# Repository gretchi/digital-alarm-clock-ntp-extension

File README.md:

# digital-alarm-clock-ntp-extension

## ボタン配置

## フロー

### ブート

1. ネットワーク確立
2. NTP日時取得

### 電源投入直後

1. `Btn_1` High -> Low (時計を開始)

### 日時合わせ

1. ボタン操作回数を計算し、操作開始をスケジュール
    1. ssが正時となるタイミングにmm + 1回目のエミュレートが行われるようエミュレート開始タイミングをスケジュール
2. `Btn_1` High -> Low
3. `Btn_A` hh++
4. `Btn_B` mm++

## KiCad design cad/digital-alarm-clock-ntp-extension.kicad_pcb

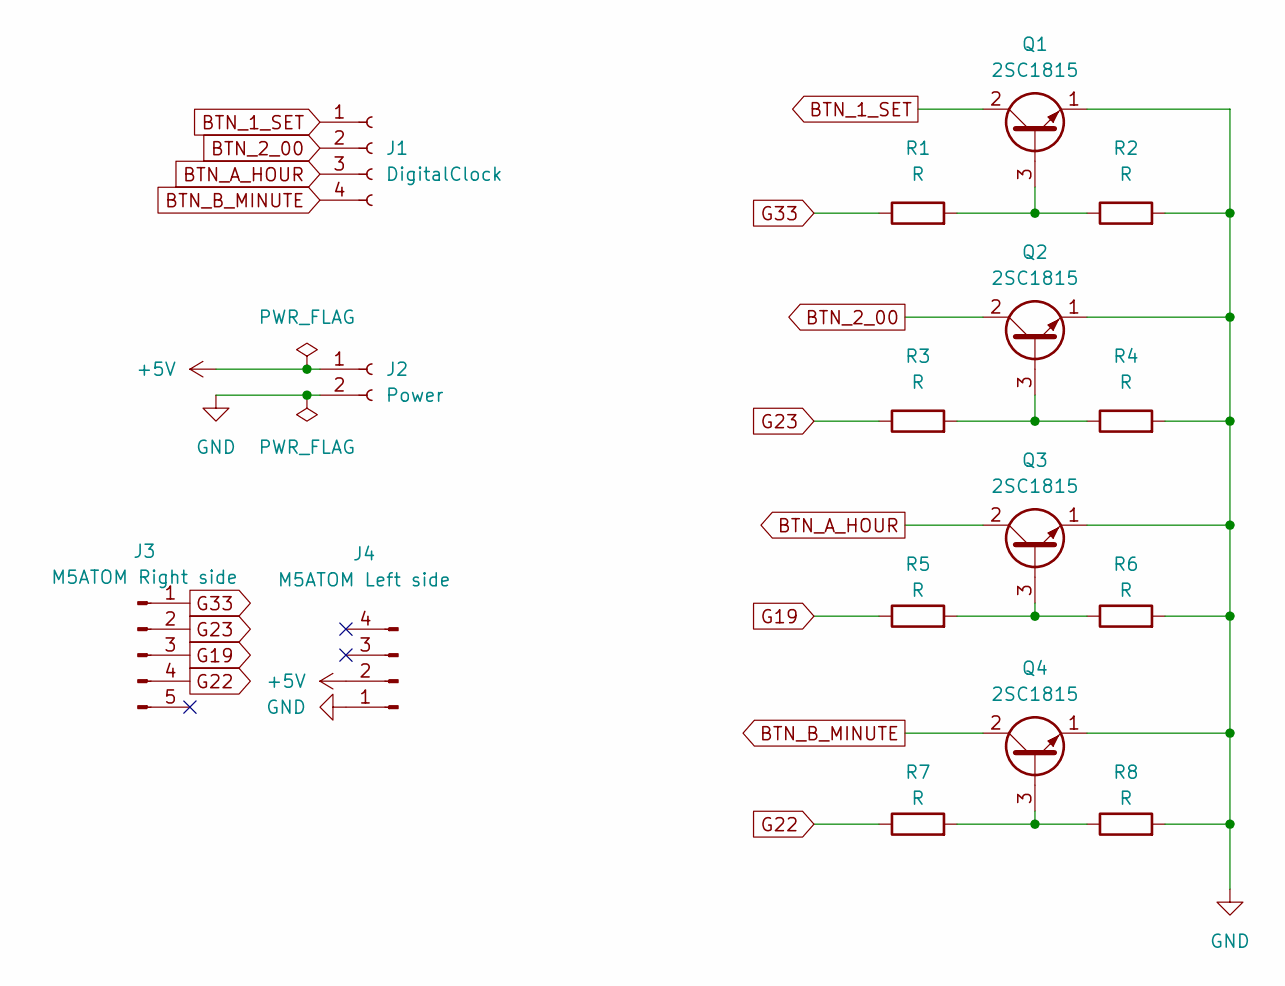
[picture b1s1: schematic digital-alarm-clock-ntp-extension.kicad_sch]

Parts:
J1: DigitalClock; JST_XH_B4B-XH-A_1x04_P2.50mm_Vertical
J2: Power; JST_XH_B2B-XH-A_1x02_P2.50mm_Vertical
J3: M5ATOM Right side; PinHeader_1x05_P2.54mm_Vertical
J4: M5ATOM Left side; PinHeader_1x04_P2.54mm_Vertical
Q1, Q2, Q3, Q4: 2SC1815; TO-92_Inline_Wide
R1, R3, R5, R7: R; R_Axial_DIN0207_L6.3mm_D2.5mm_P10.16mm_Horizontal
R2, R4, R6, R8: R; R_Axial_DIN0204_L3.6mm_D1.6mm_P5.08mm_Vertical

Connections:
+5V: J2.1, J4.2
BTN_1_SET: J1.1, Q1.2 (C)
BTN_2_00: J1.2, Q2.2 (C)
BTN_A_HOUR: J1.3, Q3.2 (C)
BTN_B_MINUTE: J1.4, Q4.2 (C)
G19: J3.3, R5.1
G22: J3.4, R7.1
G23: J3.2, R3.1
G33: J3.1, R1.1
GND: J2.2, J4.1, Q1.1 (E), Q2.1 (E), Q3.1 (E), Q4.1 (E), R2.2, R4.2, R6.2, R8.2
unnamed: Q1.3 (B), R1.2, R2.1
unnamed: Q2.3 (B), R3.2, R4.1
unnamed: Q3.3 (B), R5.2, R6.1
unnamed: Q4.3 (B), R7.2, R8.1

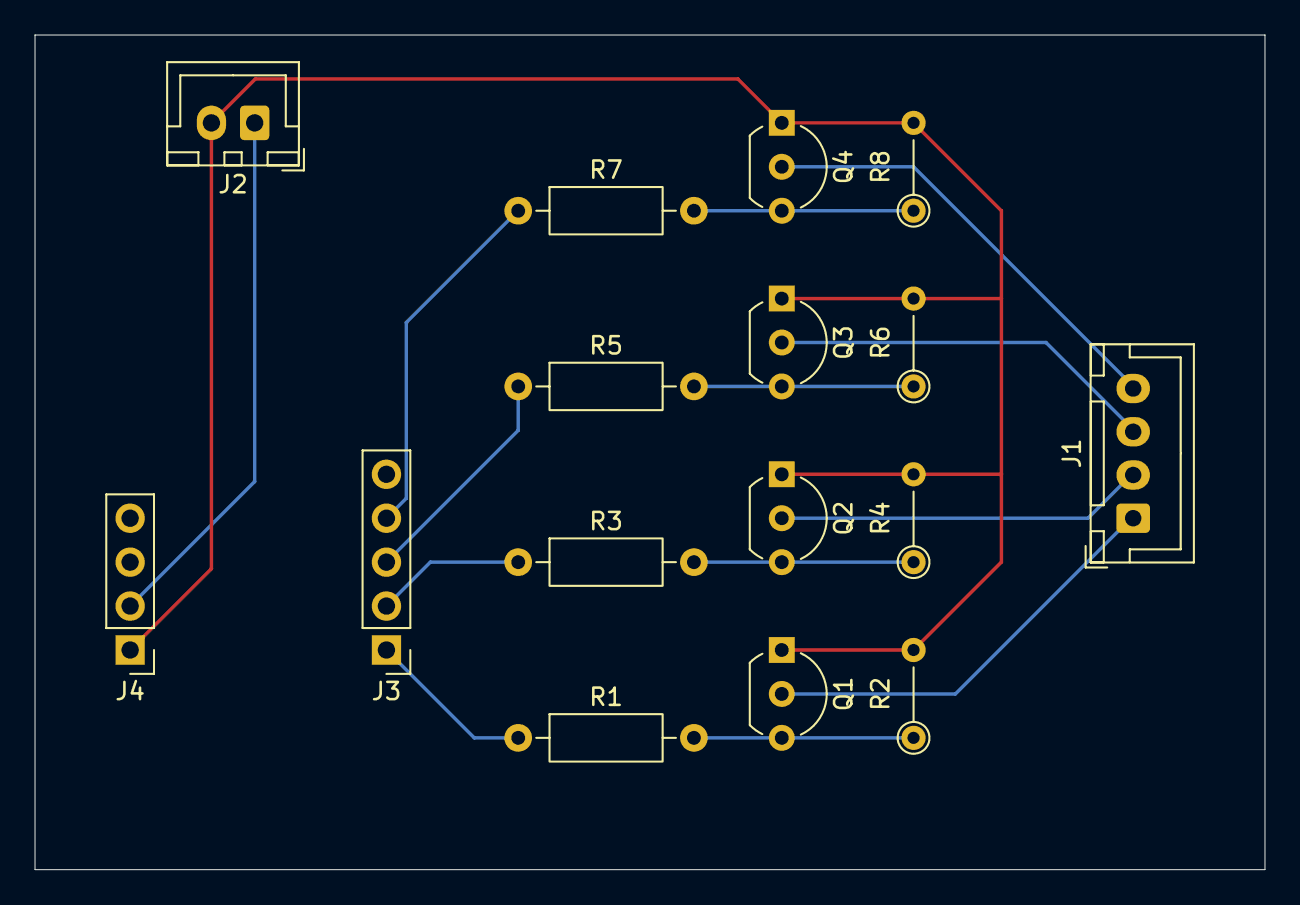
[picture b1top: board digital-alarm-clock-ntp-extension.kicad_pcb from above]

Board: 2 copper layers, 71.1 x 48.3 mm, 16 parts (0 on the bottom side), 14 nets.

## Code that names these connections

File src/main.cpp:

#include <Arduino.h>
#include <M5Atom.h>
#include <WiFiManager.h>
#include <WiFi.h>
#include "app_wifi.h"

const int BTN_1_SET = 33;
const int BTN_2_00 = 23;
const int BTN_A_HOUR = 19;
const int BTN_B_MINUTE = 22;
const int PRESS_MS = 100;

extern WiFiManager wm;
extern String configure_ssid;
extern String configure_password;

void press_ms(int gpio, int ms);

void setup()
{
    M5.begin(true, false, true);
    Serial.begin(115200);
    M5.dis.drawpix(0, 0xFF0000);

    pinMode(BTN_1_SET, INPUT);
    pinMode(BTN_2_00, INPUT);
    pinMode(BTN_A_HOUR, INPUT);
    pinMode(BTN_B_MINUTE, INPUT);

    initAppWiFi();
    Serial.printf("Configure Wi-Fi SSID: %s, Password: %s\n", configure_ssid.c_str(), configure_password.c_str());
    if (WiFiConnect() == 0)
    {
        Serial.println("Wi-Fi not connecting");
    }
    M5.dis.drawpix(0, 0x008000);

    press_ms(BTN_1_SET, PRESS_MS);
    delay(5000);

    press_ms(BTN_1_SET, PRESS_MS);
    for (int i = 0; i < 3; i++)
    {
        press_ms(BTN_A_HOUR, PRESS_MS);
        delay(300);
    }
    for (int i = 0; i < 15; i++)
    {
        press_ms(BTN_B_MINUTE, PRESS_MS);
        delay(300);
    }
}

void press_ms(int gpio, int ms)
{
    pinMode(gpio, OUTPUT);
    M5.dis.drawpix(0, 0x0080FF);
    digitalWrite(gpio, HIGH);
    delay(ms);
    pinMode(gpio, INPUT);
    M5.dis.drawpix(0, 0x008000);
    delay(ms);
}

void loop()
{
    M5.update();
    delay(100);
}

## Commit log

2025-09-18 feat(custom):
    platform io プロジェクト作成
2025-09-25 feat(custom):
    動作確認用ソース
2025-09-26 feat(custom):
    cad
2025-10-03 feat: 回路図、基板のピンアサインの修正
2025-10-03 add 動作確認用の点滅を追加
2025-10-03 feat(custom):
    wi-fi接続とボタン定義
